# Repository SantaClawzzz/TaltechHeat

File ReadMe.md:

# Introduction

DIY reflow solder plate controller design, where the actual plate connects with XT30 connector.<br>
Based on this [`PROJECT`](https://github.com/DerSpatz/PCB-reflow-solder-heat-plate)

All PDFs, images, and exports are under the [OUTPUTS](https://github.com/SantaClawzzz/TaltechHeat/tree/master/Outputs) folder

The BOM file is also there and the basket for it is [HERE](https://www.mouser.ee/Tools/SavedCart/Share?AccessID=80928401d5)

## Hardware:<br> 
- **20V 5A max**
- USB-C PD **(Power Delivery)** - `[STUSB4500]`
- MCU programmed with SWD - `[STM32F103C6]`
- 5V switching regulator - `[AP64060ZQ]`

## Pinout

|  User    |   Pin  |
|----------|--------|
|   BUT1   |  PC13  |
|   BUT2   |  PC14  |
|   PC15   |  PC15  |

| Signal     | Pin  | Function       |
|------------|------|----------------|
| SCL        | PB8  | I2C1_SCL       |
| SDA        | PB9  | I2C1_SDA       |
| PD_ALERT   | PB10 |                |
| PD_RST     | PB11 |                |
| PWM        | PB13 | TIM1_CH1N      |
| PD_GPIO    | PB14 |                |
| PD_ATTACH  | PB15 |                |
| VCC-DIV    | PA3  | ADC1_IN3       |
| TEMP1      | PA4  | ADC1_IN4       | 
| TEMP2      | PA5  | ADC1_IN5       |
| POWER_OK_3 | PA8  |                |
| UART1_RX   | PA9  | USART1_TX      |
| UART1_TX   | PA10 | USART1_RX      |
| SWDIO      | PA13 | SYS_JTMS-SWDIO |
| SWCLK      | PA14 | SYS_JTCK-SWCLK |

## Problems

- SWD pins not brought out to headers
- MOSFET too small, can't handle current (PD FET)
- PWM not on PWM capable pin
- Routing issues

- [More detail](https://docs.google.com/document/d/1i9aejrMOuASw6s5gDh6MXbNuGSY3eZ5T1xDJf5HSRbU/edit?tab=t.0)

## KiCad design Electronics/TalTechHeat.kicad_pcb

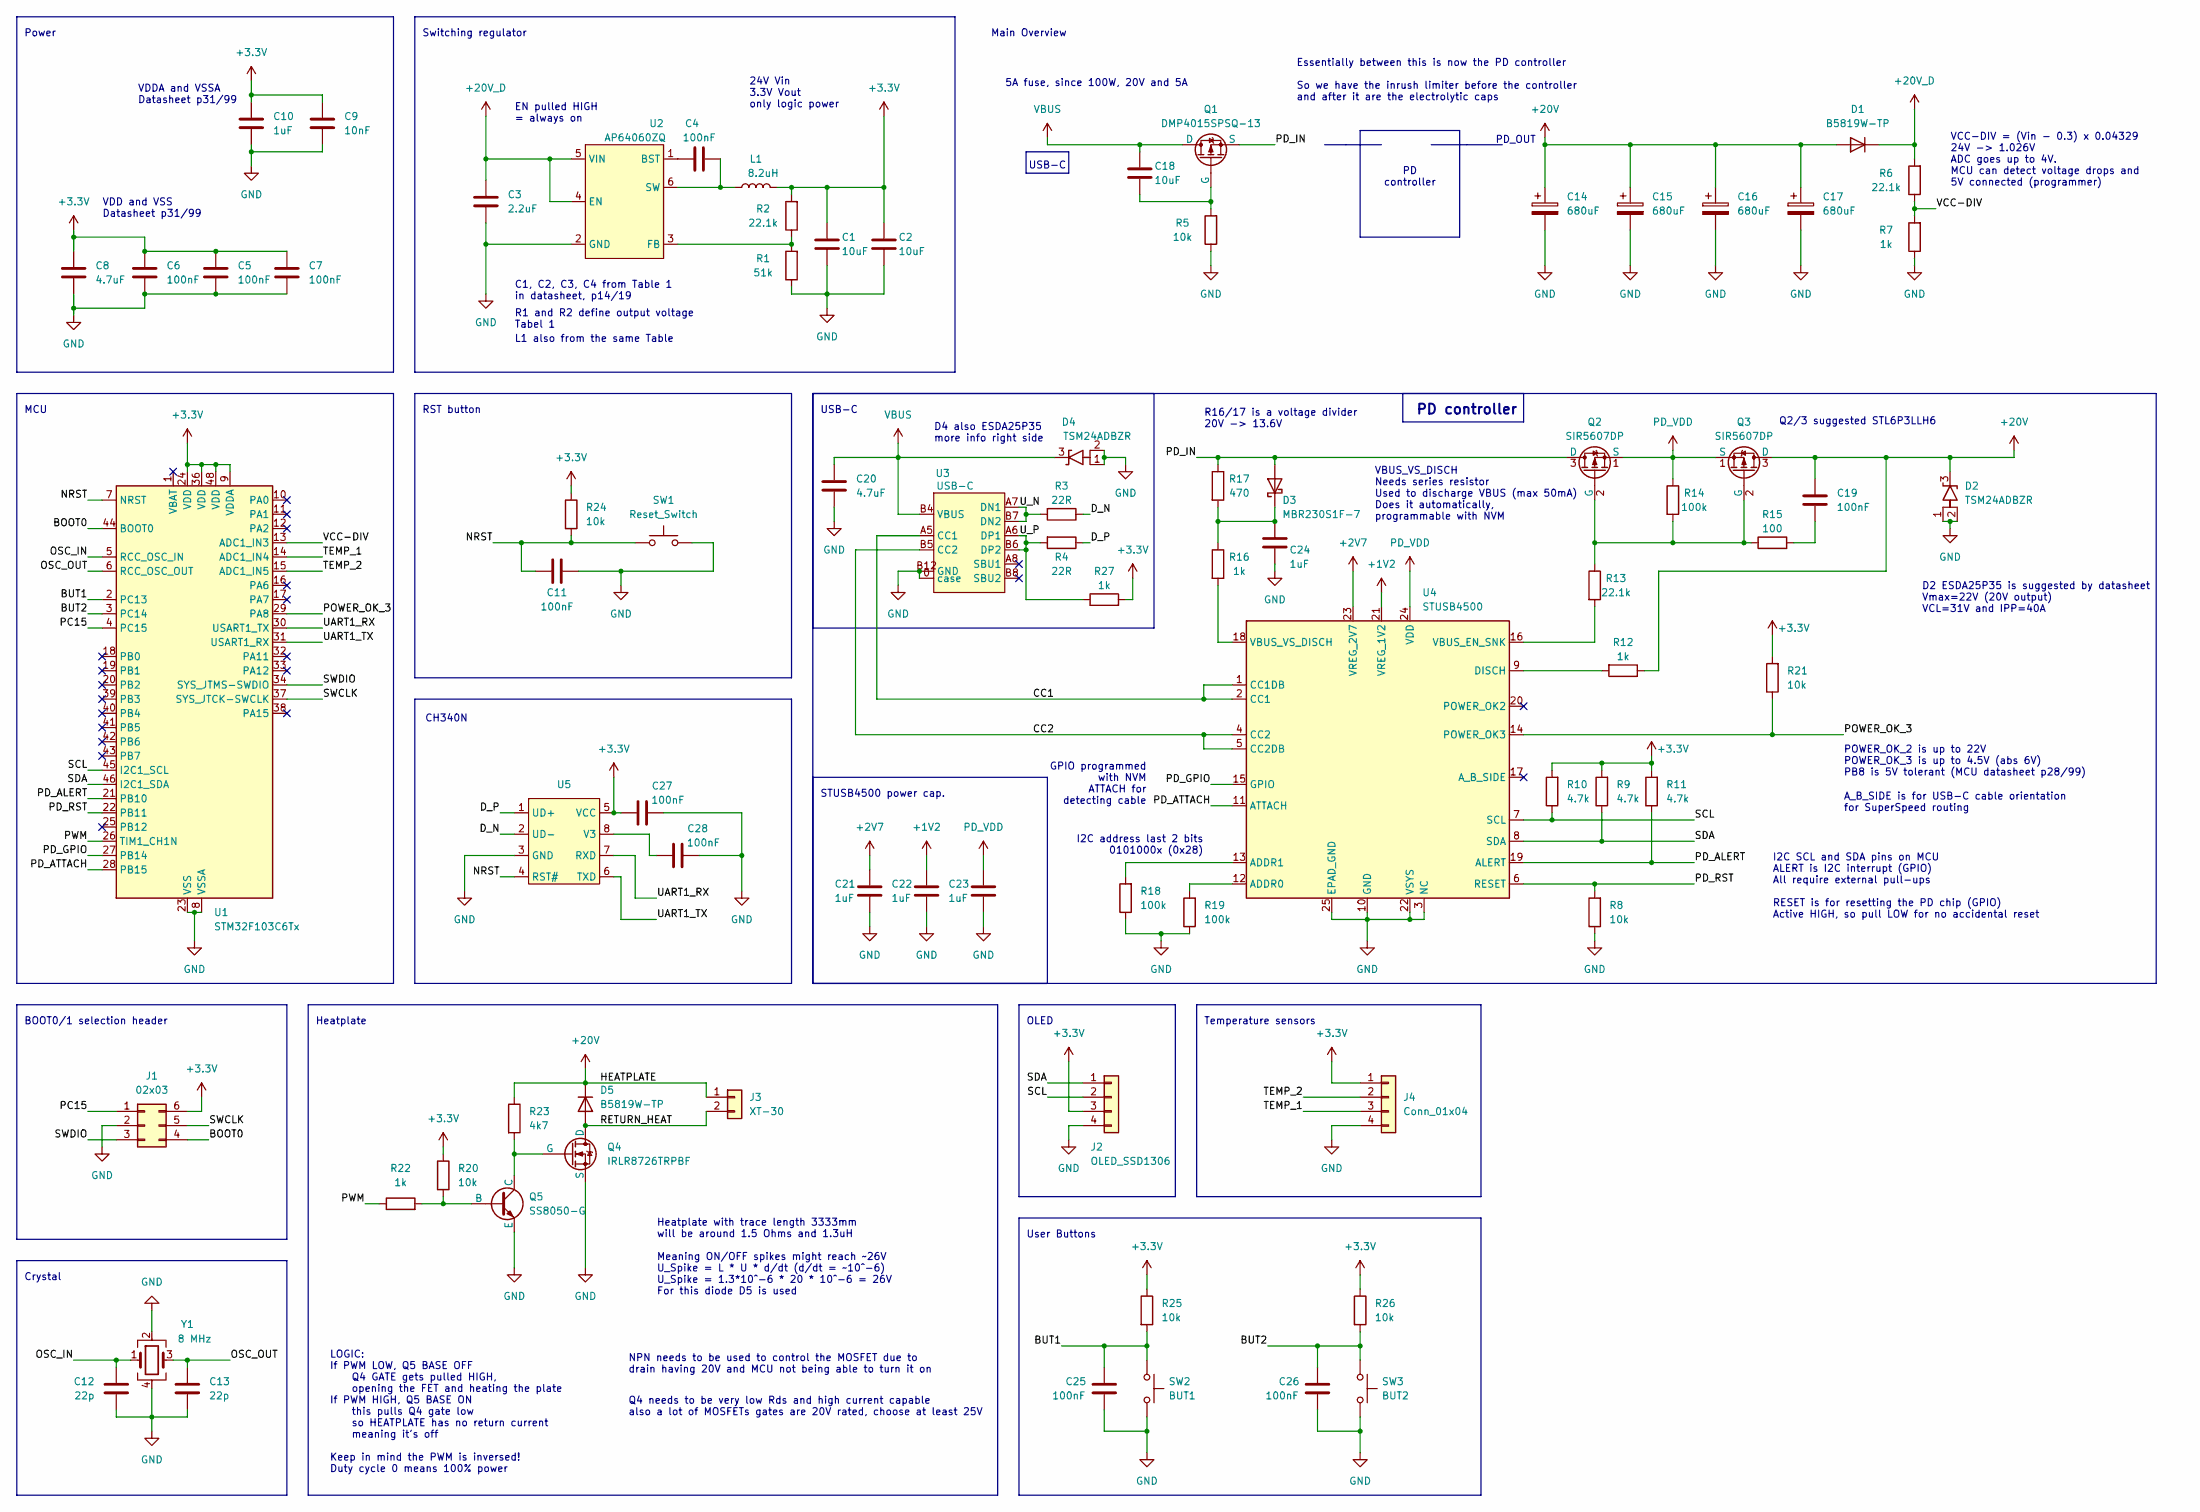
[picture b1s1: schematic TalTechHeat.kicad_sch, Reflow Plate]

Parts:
C1, C2, C18: 10uF; C_1206_3216Metric_Pad1.33x1.80mm_HandSolder; MPN CL31B106KBHNNNE; Mouser_PN 187-CL31B475KBHNFNE
C3: 2.2uF; C_0805_2012Metric_Pad1.18x1.45mm_HandSolder; MPN CL31B225KBHNNNE; Mouser_PN 187-CL31B225KBHNNNE
C4, C5, C6, C7, C11, C19, C25, C26, C27, C28: 100nF; C_0603_1608Metric_Pad1.08x0.95mm_HandSolder; MPN CL10B104KC8NNNC; Mouser_PN 187-CL10B104KC8NNNC
C8, C20: 4.7uF; C_1206_3216Metric_Pad1.33x1.80mm_HandSolder; MPN CL31B475KBHNFNE; Mouser_PN 187-CL31B475KBHNFNE
C9: 10nF; C_0603_1608Metric_Pad1.08x0.95mm_HandSolder; MPN CL10B103KB8NNNL; Mouser_PN 187-CL10B103KB8NNNL
C10, C21, C22, C23, C24: 1uF; C_0805_2012Metric_Pad1.18x1.45mm_HandSolder; MPN CL21B105KBFNNNE; Mouser_PN 187-CL21B105KBFNNNE
C12, C13: 22p; C_0603_1608Metric_Pad1.08x0.95mm_HandSolder; MPN CL10C220JB8NNNC; Mouser_PN 187-CL10C220JB8NNNC
C14, C15, C16, C17: 680uF; 10mm CAP; MPN UHW1V681MPD; Mouser_PN 647-UHW1V681MPD
D1, D5: B5819W-TP; D_SOD-123; MPN B5819W-TP; Mouser_PN 833-B5819W-TP
D2, D4: TSM24ADBZR; SOT-23-3; MPN TSM24ADBZR; Mouser_PN 595-TSM24ADBZR
D3: MBR230S1F-7; D_SOD-123F; MPN MBR230S1F-7; Mouser_PN 621-MBR230S1F-7
J1: 02x03; PinHeader_2x03_P2.54mm_Vertical; MPN 10129381-906004BLF; Mouser_PN 649-1012938190604BLF
J2: OLED_SSD1306; OLED_128x32; MPN SSD1306 128x32; Mouser_PN (Endal olemas)
J3: XT-30; AMASS_XT30PW-F_1x02_P2.50mm_Horizontal; MPN XT30PW-F; Mouser_PN (Endal olemas)
J4: Conn_01x04; JST_PH_B4B-PH-K_1x04_P2.00mm_Vertical; MPN B4B-PH-K-S(LF)(SN); Mouser_PN 306-B4BPHKSLFSNPP
L1: 8.2uH; L_Vishay_IHLP-2525; MPN IHLP2525BDER8R2M01; Mouser_PN 70-IHLP2525BDER8R2M1
Q1: DMP4015SPSQ-13; DMP4015; MPN DMP4015SPSQ-13; Mouser_PN 621-DMP4015SPSQ-13
Q2, Q3: SIR5607DP
Q4: IRLR8726TRPBF; TO-252.2; MPN IRLR8726TRPBF; Mouser_PN 942-IRLR8726TRPBF
Q5: SS8050-G; SOT-23-3; MPN SS8050-G; Mouser_PN 750-SS8050-G
R1: 51k; R_0603_1608Metric_Pad0.98x0.95mm_HandSolder; MPN RMC16K513FTP; Mouser_PN 791-RMC16K513FTP
R2, R6, R13: 22.1k; R_0603_1608Metric_Pad0.98x0.95mm_HandSolder; MPN RT0603FRE1322K1L; Mouser_PN 603-RT0603FRE1322K1L
R3, R4: 22R; R_0603_1608Metric_Pad0.98x0.95mm_HandSolder; MPN RMC1/16K22R0FTP; Mouser_PN 791-RMC1/16K22R0FTP
R5, R8: 10k; R_0603_1608Metric_Pad0.98x0.95mm_HandSolder; MPN AF0603FR-0710KL; Mouser_PN 603-AF0603FR-0710KL %3D
R7, R12, R16, R22, R27: 1k; R_0603_1608Metric_Pad0.98x0.95mm_HandSolder; MPN CRCW06031K00FKEE; Mouser_PN 71-CRCW06031K00FKEE
R9, R10, R11: 4.7k; R_0603_1608Metric_Pad0.98x0.95mm_HandSolder; MPN RC0603JR-074K7P; Mouser_PN 603-RC0603JR-074K7P
R14, R18, R19: 100k; R_0603_1608Metric_Pad0.98x0.95mm_HandSolder; MPN RCA0603100KFKEC; Mouser_PN 71-RCA0603100KFKEC
R15: 100; R_0603_1608Metric_Pad0.98x0.95mm_HandSolder; MPN RT0603FRE10100RL; Mouser_PN 603-RT0603FRE10100RL
R17: 470; R_0603_1608Metric_Pad0.98x0.95mm_HandSolder; MPN AC0603JR-7W470RL; Mouser_PN 603-AC0603JR-7W470RL
R20, R21, R24, R25, R26: 10k; R_0603_1608Metric_Pad0.98x0.95mm_HandSolder; MPN AF0603FR-0710KL; Mouser_PN 603-AF0603FR-0710KL
R23: 4k7; R_0603_1608Metric_Pad0.98x0.95mm_HandSolder; MPN AF0603FR-074K7L; Mouser_PN 603-AF0603FR-074K7L
SW1: Reset_Switch; SW_Push_1P1T_NO_Vertical_Wuerth_434133025816; MPN 434133025816; Mouser_PN 710-434133025816
SW2: BUT1; SW_PUSH_6mm_H4.3mm; MPN TS02-66-50-BK-100-LCR-D; Mouser_PN 179-TS026650BK100LCR
SW3: BUT2; SW_PUSH_6mm_H4.3mm; MPN TS02-66-50-BK-100-LCR-D; Mouser_PN 179-TS026650BK100LCR
U1: STM32F103C6Tx; LQFP-48_7x7mm_P0.5mm; MPN STM32F103C6T7A; Mouser_PN 511-STM32F103C6T7A
U2: AP64060ZQ; TSOT26; MPN AP64060ZQ; Mouser_PN 621-AP64060ZQWU-7
U3: USB-C; USB4085; MPN USB4085-GF-A; Mouser_PN 640-USB4085-GF-A
U4: STUSB4500; QFN50P400X400X100-25N-D; MPN STUSB4500QTR; Mouser_PN 511-STUSB4500QTR
U5: SOP-8_3.76x4.96mm_P1.27mm
Y1: 8 MHz; ECS-80-12-33Q-GN; MPN ECS-80-12-33Q-GN-TR; Mouser_PN 520-80-12-33Q-GN-TR

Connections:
+1V2: C22.1, U4.21 (VREG_1V2)
+2V7: C21.1, U4.23 (VREG_2V7)
+3.3V: C1.1, C2.1, C5.1, C6.1, C7.1, C8.1, C9.1, C10.1, C27.1, J1.6, J2.3, J4.1, L1.2, R2.2, R9.2, R10.2, R11.2, R20.1, R21.2, R24.1, R25.1, R26.1, R27.2, U1.9 (VDDA), U1.24 (VDD), U1.36 (VDD), U1.48 (VDD), U5.5 (VCC)
+20V: C14.1, C15.1, C16.1, C17.1, C19.1, D1.2 (A), D2.3 (A3), D5.1 (K), J3.1, Q3.3 (D), R12.1, R23.1
+20V_D: C3.1, D1.1 (K), R6.2, U2.4 (EN), U2.5 (VIN)
/BOOT0: J1.4, U1.44 (BOOT0)
/BUT1: C25.1, R25.2, SW2.1, U1.2 (PC13)
/BUT2: C26.1, R26.2, SW3.1, U1.3 (PC14)
/CC1: U3.A5 (CC1), U4.1 (CC1DB), U4.2 (CC1)
/CC2: U3.B5 (CC2), U4.4 (CC2), U4.5 (CC2DB)
/D_N: R3.1, U5.2 (UD-)
/D_P: R4.1, U5.1 (UD+)
/NRST: C11.1, R24.2, SW1.1, U1.7 (NRST), U5.4 (RST#)
/OSC_IN: C12.1, U1.5 (RCC_OSC_IN), Y1.1
/OSC_OUT: C13.1, U1.6 (RCC_OSC_OUT), Y1.3
/PC15: J1.1, U1.4 (PC15)
/PD_ALERT: R11.1, U1.21 (PB10), U4.19 (ALERT)
/PD_ATTACH: U1.28 (PB15), U4.11 (ATTACH)
/PD_GPIO: U1.27 (PB14), U4.15 (GPIO)
/PD_IN: D3.2 (A), Q1.3 (S), Q2.3 (D), R17.1
/PD_RST: R8.2, U1.22 (PB11), U4.6 (RESET)
/POWER_OK_3: R21.1, U1.29 (PA8), U4.14 (POWER_OK3)
/PWM: R22.1, U1.26 (TIM1_CH1N)
/RETURN_HEAT: D5.2 (A), J3.2, Q4.1 (D)
/SCL: J2.2, R10.1, U1.45 (I2C1_SCL), U4.7 (SCL)
/SDA: J2.1, R9.1, U1.46 (I2C1_SDA), U4.8 (SDA)
/SWCLK: J1.5, U1.37 (SYS_JTCK-SWCLK)
/SWDIO: J1.3, U1.34 (SYS_JTMS-SWDIO)
/TEMP_1: J4.3, U1.14 (ADC1_IN4)
/TEMP_2: J4.2, U1.15 (ADC1_IN5)
/UART1_RX: U1.30 (USART1_TX), U5.7 (RXD)
/UART1_TX: U1.31 (USART1_RX), U5.6 (TXD)
/U_N: R3.2, U3.A7 (DN1), U3.B7 (DN2)
/U_P: R4.2, R27.1, U3.A6 (DP1), U3.B6 (DP2)
/VCC-DIV: R6.1, R7.2, U1.13 (ADC1_IN3)
GND: C1.2, C2.2, C3.2, C5.2, C6.2, C7.2, C8.2, C9.2, C10.2, C11.2, C12.2, C13.2, C14.2, C15.2, C16.2, C17.2, C20.2, C21.2, C22.2, C23.2, C24.2, C25.2, C26.2, C27.2, C28.2, D2.1 (A1), D2.2 (A2), D4.1 (A1), D4.2 (A2), J1.2, J2.4, J4.4, Q4.3 (S), Q5.3 (E), R1.1, R5.1, R7.1, R8.1, R18.1, R19.1, SW1.2, SW2.2, SW3.2, U1.8 (VSSA), U1.23 (VSS), U1.35 (VSS), U1.47 (VSS), U2.2 (GND), U3.0 (case), U3.A1 (GND), U3.A12 (GND), U3.B1 (GND), U3.B12 (GND), U4.3 (NC), U4.10 (GND), U4.22 (VSYS), U4.25 (EPAD_GND), U5.3 (GND), Y1.2, Y1.4
unnamed: C19.2, R15.2
unnamed: C24.1, D3.1 (K), R16.1, R17.2
unnamed: C18.2, Q1.2 (G), R5.2
unnamed: Q2.2 (G), Q3.2 (G), R13.1, R14.2, R15.1
unnamed: Q4.2 (G), Q5.1 (C), R23.2
unnamed: Q5.2 (B), R20.2, R22.2
unnamed: C4.1, U2.1 (BST)
unnamed: R1.2, R2.1, U2.3 (FB)
unnamed: C4.2, L1.1, U2.6 (SW)
unnamed: R19.2, U4.12 (ADDR0)
unnamed: R18.2, U4.13 (ADDR1)
unnamed: R12.2, U4.9 (DISCH)
unnamed: R13.2, U4.16 (VBUS_EN_SNK)
unnamed: R16.2, U4.18 (VBUS_VS_DISCH)
unnamed: C28.1, U5.8 (V3)
PD_VDD: C23.1, Q2.1 (S), Q3.1 (S), R14.1, U4.24 (VDD)
VBUS: C18.1, C20.1, D4.3 (A3), Q1.1 (D), U3.A4 (VBUS), U3.A9 (VBUS), U3.B4 (VBUS), U3.B9 (VBUS)

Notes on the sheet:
R16/17 is a voltage divider 20V -> 13.6V
CH340N
PD_OUT
Main Overview
EN pulled HIGH = always on
24V Vin 3.3V Vout only logic power
STUSB4500 power cap.
POWER_OK_2 is up to 22V POWER_OK_3 is up to 4.5V (abs 6V) PB8 is 5V tolerant (MCU datasheet p28/99)
R1 and R2 define output voltage Tabel 1
Q4 needs to be very low Rds and high current capable also a lot of MOSFETs gates are 20V rated, choose at least 25V
NPN needs to be used to control the MOSFET due to drain having 20V and MCU not being able to turn it on
USB-C
PD controller
GPIO programmed with NVM ATTACH for detecting cable
User Buttons
D4 also ESDA25P35 more info right side
LOGIC: If PWM LOW, Q5 BASE OFF Q4 GATE gets pulled HIGH, opening the FET and heating the plate If PWM HIGH, Q5 BASE ON this pulls Q4 gate low so HEATPLATE has no return current meaning it's off Keep in mind the PWM is inversed! Duty cycle 0 means 100% power
Switching regulator
Q2/3 suggested STL6P3LLH6
Heatplate with trace length 3333mm will be around 1.5 Ohms and 1.3uH Meaning ON/OFF spikes might reach ~26V U_Spike = L * U * d/dt (d/dt = ~10^-6) U_Spike = 1.3*10^-6 * 20 * 10^-6 = 26V For this diode D5 is used
C1, C2, C3, C4 from Table 1 in datasheet, p14/19
L1 also from the same Table
A_B_SIDE is for USB-C cable orientation for SuperSpeed routing
VDDA and VSSA Datasheet p31/99
VBUS_VS_DISCH Needs series resistor Used to discharge VBUS (max 50mA) Does it automatically, programmable with NVM
D2 ESDA25P35 is suggested by datasheet Vmax=22V (20V output) VCL=31V and IPP=40A
Crystal
OLED
Essentially between this is now the PD controller So we have the inrush limiter before the controller and after it are the electrolytic caps
Power
VCC-DIV = (Vin - 0.3) x 0.04329 24V -> 1.026V ADC goes up to 4V. MCU can detect voltage drops and 5V connected (programmer)
Temperature sensors
Heatplate
VDD and VSS Datasheet p31/99
MCU
I2C address last 2 bits 0101000x (0x28)
5A fuse, since 100W, 20V and 5A
BOOT0/1 selection header
PD controller
I2C SCL and SDA pins on MCU ALERT is I2C interrupt (GPIO) All require external pull-ups RESET is for resetting the PD chip (GPIO) Active HIGH, so pull LOW for no accidental reset

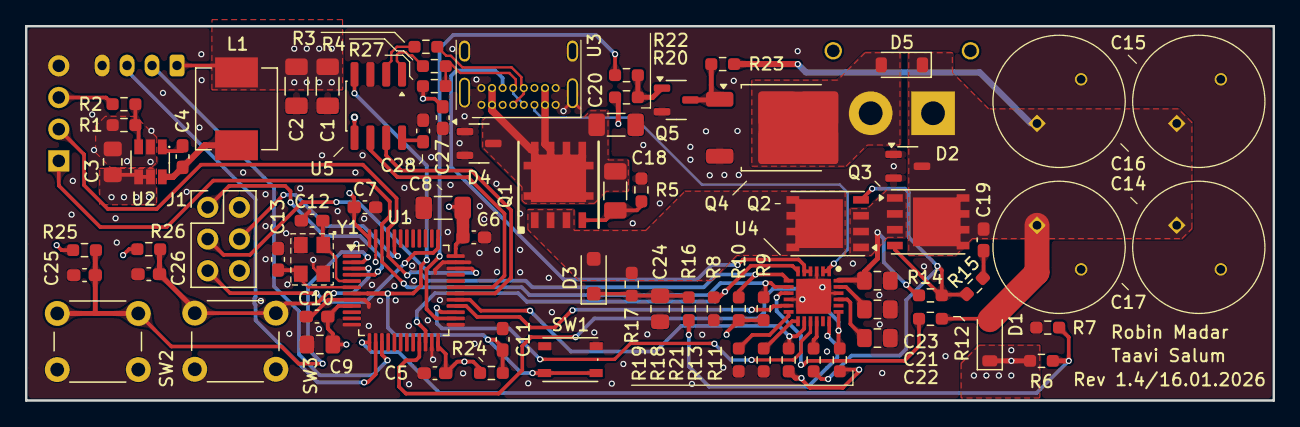
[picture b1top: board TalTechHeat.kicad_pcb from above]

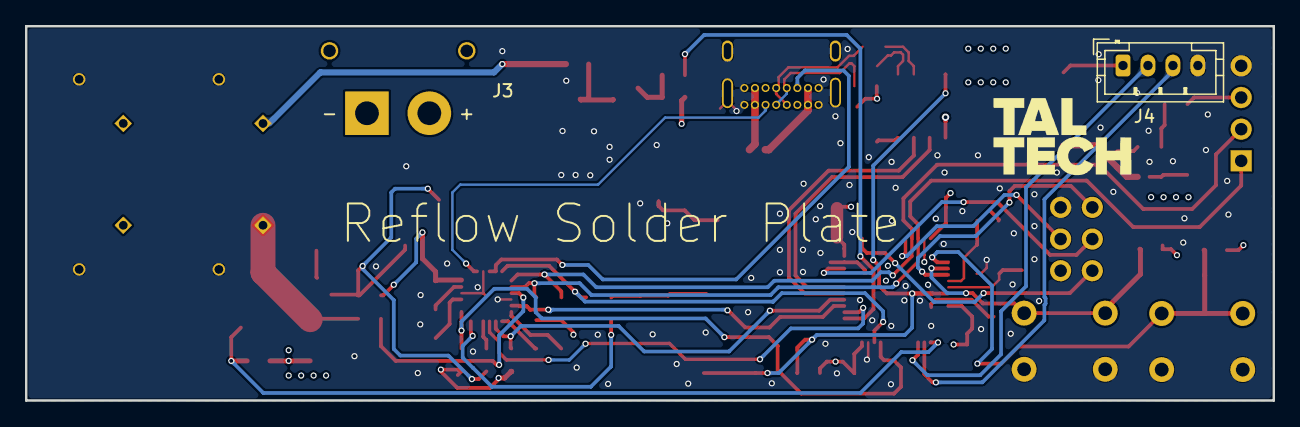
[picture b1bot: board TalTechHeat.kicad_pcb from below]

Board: 4 copper layers, 100.0 x 30.0 mm, 79 parts (2 on the bottom side), 53 nets.

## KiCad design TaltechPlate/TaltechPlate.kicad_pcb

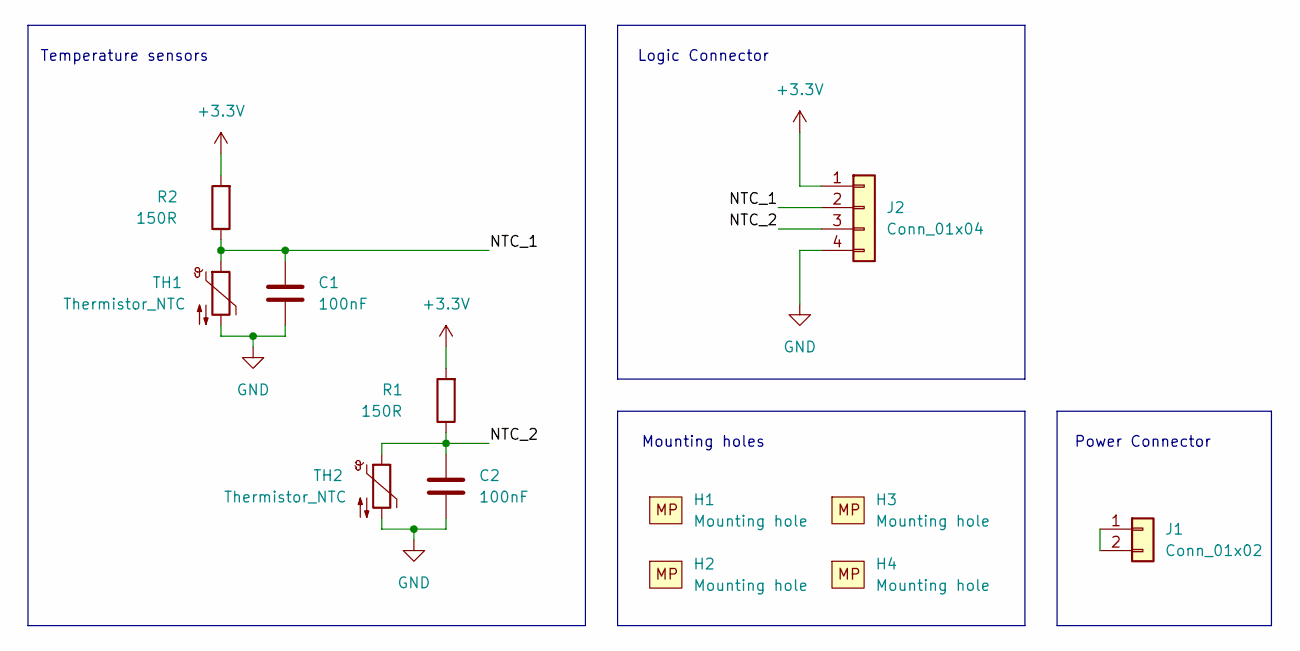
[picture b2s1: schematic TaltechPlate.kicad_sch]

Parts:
C1, C2: 100nF; C_0603_1608Metric; MPN CL10B104KC8NNNC; Mouser_PN 187-CL10B104KC8NNNC
H1, H2, H3, H4: Mounting hole; MountingHole_3.2mm_M3_DIN965
J1: Conn_01x02; AMASS_XT30U-M_1x02_P5.0mm_Vertical; MPN XT-30
J2: Conn_01x04; JST_PH_B4B-PH-K_1x04_P2.00mm_Vertical; MPN B4B-PH-K-S(LF)(SN); Mouser_PN 306-B4BPHKSLFSNPP
R1, R2: 150R; R_0603_1608Metric; MPN RC0603FR-10150RL; Mouser_PN 603-RC0603FR-10150RL
TH1, TH2: Thermistor_NTC; D_MiniMELF; MPN SM102B1K; Mouser_PN 803-SM102B1K

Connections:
+3.3V: J2.1, R1.2, R2.2
/NTC_1: C1.1, J2.2, R2.1, TH1.1
/NTC_2: C2.1, J2.3, R1.1, TH2.1
GND: C1.2, C2.2, J2.4, TH1.2, TH2.2
unnamed: J1.1, J1.2

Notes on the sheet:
Mounting holes
Logic Connector
Power Connector
Temperature sensors

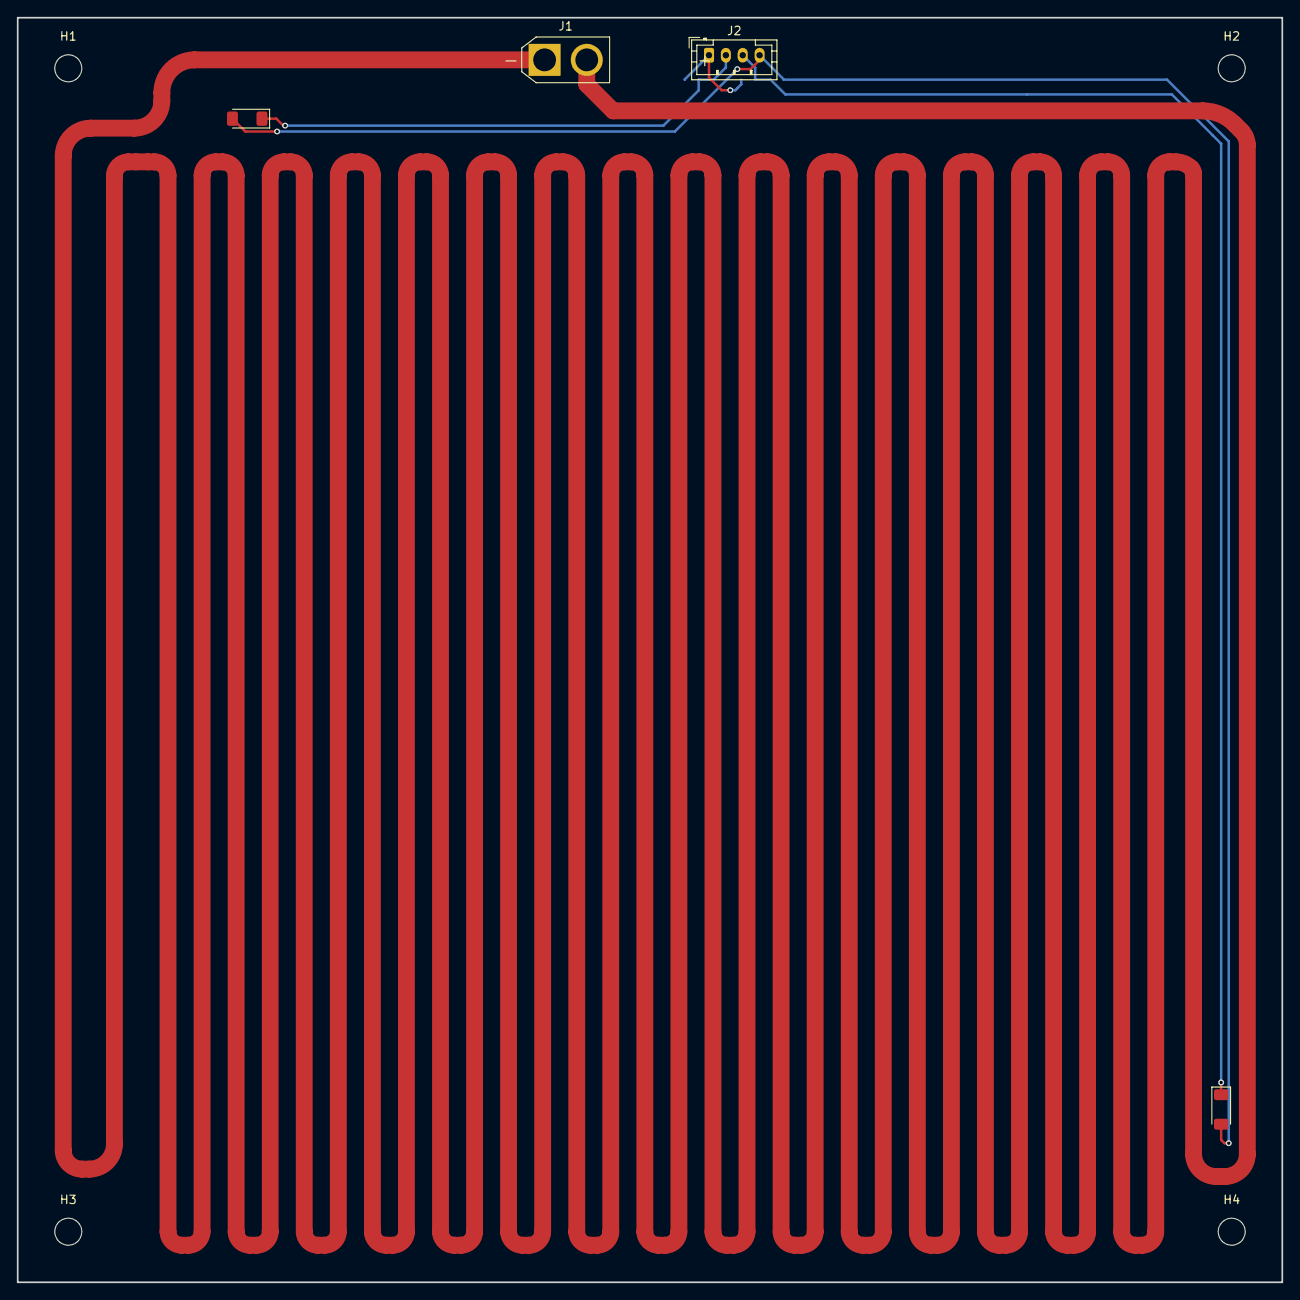
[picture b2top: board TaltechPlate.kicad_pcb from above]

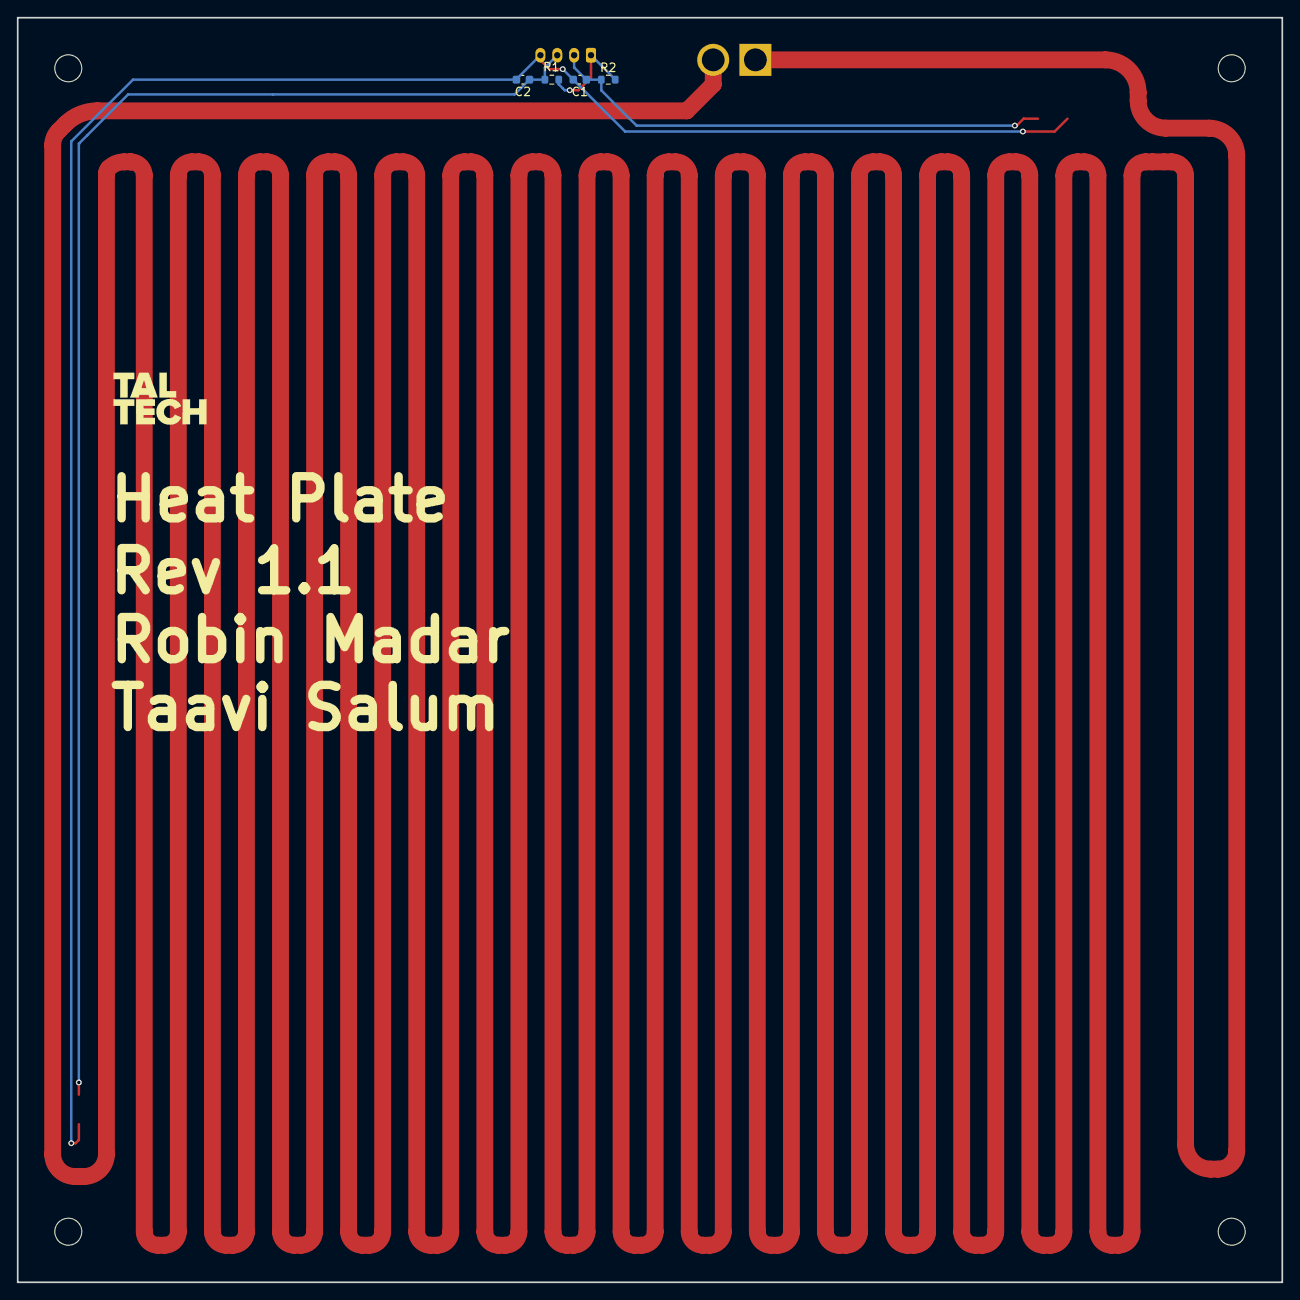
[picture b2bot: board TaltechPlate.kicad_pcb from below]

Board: 2 copper layers, 150.0 x 150.0 mm, 12 parts (4 on the bottom side), 5 nets.

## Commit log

2026-01-02 Rev 1
2026-01-02 Exports
2026-01-02 Pics
2026-01-03 Updated changes Rev 1.1
2026-01-05 Rev 1.2
2026-01-05 Added the silkscreen as well
2026-01-05 Updated the page parameters in pdf
2026-01-10 Silckscreen changes and BOM changes
2026-01-10 Forgot to update exports
2026-01-10 Rev 1.3, one resistor and exports update
2026-01-13 Removed boot1, added UART
2026-01-15 Test after directory change
2026-01-16 TaltechPlate folder Rev1, no Titleblock yet
2026-01-16 Updated new parts MFN and MPN as well as title block
2026-01-19 Mounting holes and longer trace on plate
2026-01-19 Export update
2026-02-02 Remove invalid Windows path files
2026-02-02 removed broken kleplace
2026-05-23 ReadMe
2026-05-23 Fixes implementation 1/2
2026-05-25 Fet replace and directory change
